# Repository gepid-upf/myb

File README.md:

# Move Your Body

Code provided in this repository gets the raw data from MPU-6050 and MAX30100, calculates a step counter and heart rate, and stores it in the ESP-32 SPIFFS to be send via bluetooth to the MYB App.

## Table of Contents

- [Components](#components)
  - [ESP 32](#esp-32)
  - [ESP-IDF](#esp-idf)
  - [MPU-6050](#mpu-6050)
  - [MAX30100](#max30100)
- [Quick Start](#quick-start)
  - [Connect](#connect)
  - [Configuration and Flash](#configuration-and-flash)
- [How It Works](#how-it-works)
- [Next Steps](#next-steps)
  - [Software](#software)
- [License](#license)
- [Acknowledgments](#acknowledgments)

## Components

To make this code work, you need the following components:

* This repository. It contains submodules, so make sure you clone it with `--recursive` option. If you have already cloned it without `--recursive`, run `git submodule update --init`.
* [ESP 32](https://espressif.com/en/products/hardware/esp32/overview) module.
* [ESP-IDF](https://github.com/espressif/esp-idf).
* [MPU-6050](https://www.invensense.com/products/motion-tracking/6-axis/mpu-6050/) module.
* [MAX30100](https://www.maximintegrated.com/en/products/sensors/MAX30100.html) module.

### ESP 32

Any ESP 32 module should work.

### ESP-IDF

Configure your PC according to [ESP 32 Documentation](https://docs.espressif.com/projects/esp-idf/en/latest/?badge=latest?badge=latest). Windows, Linux and Mac OS are supported.

### MPU-6050

This example has been tested with a MPU-6050. 

The MPU-6000 should work aswell.

### MAX30100

Any MAX30100 module should work.

## Quick Start

If you have your components ready, follow this section to [connect](#connect) the components to the ESP 32 module, [flash](#configuration-and-flash) the application to the ESP 32 and monitor the data.

### Connect

The pins used in this project to connect the ESP 32 to the MPU-6050 and MAX30100 are shown in the table below. The pinout can be adjusted in the software.

| Interface | MPU-6050 Pin | MAX30100 Pin | ESP 32 DevKitC Pin Mapping |
| :--- | :---: | :---: | :---: |
| I2C Serial Clock | SCL | SCL | IO25 |
| I2C Serial Data | SDA | SDA | IO26 |
| Power Supply 3.3V | VCC | VIN | 3V3 |
| Ground | GND | GND | GND |

Notes:

If the sensors are not communicating with the ESP 32, consider adding 10kΩ pull-up resistors to the SCL and SDA lines.

If you're using ESP 32 on Windows and is having the [ESP 32 Reset to Bootloader](https://github.com/espressif/esptool/issues/136) issue, add a 2.2uF capacitor conencted between GND and EN pins of ESP 32 module.

### Configuration and Flash

1. Clone the code provided in this repository to your PC.

2. To use the SPIFFS, you need a tool to create the SPIFFS partition image - we recommend using [igrr](https://github.com/igrr)'s [mkspiffs](https://github.com/igrr/mkspiffs).
After creating the SPIFFS image, use the `esptool` to flash the image binary to the module.
If you're gonna use the `partitions.csv` file, use the following configuration:
```
BLOCK SIZE = 4096
PAGE SIZE = 256
PARTITION SIZE = 0x2F0000
PARTITION OFFSET = 0x110000
```

3. On the `menuconfig`, use the following options:
```
Flash size: 4MB
Partition Table: Custom Partition Table CSV (choose the partitions.csv file)
```

4. Compile with the latest ESP-IDF installed from GitHub and download it to the module.

## How it Works

### Software

The software has 3 libraries, all located in the components folder:
* [esp32_i2c_rw.c](https://github.com/gabrielbvicari/esp32-i2c_rw/blob/f532d6a554dc2f2daa3954b597072ecb48354688/esp32_i2c_rw.c) and [include/esp32_i2c_rw.h](https://github.com/gabrielbvicari/esp32-i2c_rw/blob/f532d6a554dc2f2daa3954b597072ecb48354688/include/esp32_i2c_rw/esp32_i2c_rw.h) - implementation of the I2C protocol used by the [MPU-6050](https://github.com/gabrielbvicari/esp32-mpu6050) library.

* [mpu6050.c](https://github.com/gabrielbvicari/esp32-mpu6050/blob/fa99df4a75917e85b31b20e94344acca3d00d556/mpu6050.c), [include/mpu6050.h](https://github.com/gabrielbvicari/esp32-mpu6050/blob/fa99df4a75917e85b31b20e94344acca3d00d556/include/mpu6050/mpu6050.h) and [include/mpu6050_registers.h](https://github.com/gabrielbvicari/esp32-mpu6050/blob/fa99df4a75917e85b31b20e94344acca3d00d556/include/mpu6050/mpu6050_registers.h) - definition of the registers of the MPU-6050, setters/getters functions for the registers aswell as functions of calibration and self-test.

* [max30100.c](https://github.com/aedalzotto/esp32-max30100/blob/2585aa70b25955ecb60d2d8fb26c5cbb76526d65/max30100.c), [include/max30100.h](https://github.com/aedalzotto/esp32-max30100/blob/2585aa70b25955ecb60d2d8fb26c5cbb76526d65/include/max30100/max30100.h) and [include/registers.h](https://github.com/aedalzotto/esp32-max30100/blob/2585aa70b25955ecb60d2d8fb26c5cbb76526d65/include/max30100/registers.h) - definition of the registers of the MAX3010, setters/getters functions for the registers aswell as implementations of filters (Butterworth, DC Removal and Moving Average).

* component.mk - files used by C `make` command to access component during compilation.

Application is executed from [main.c](main/main.c) file located in main folder.
The main file has a step counter function, as well as log functions and routines that store the readings in the SPIFFS.

## Next Steps

Add the GATT Bluetooth functionality to send the data stored in the SPIFFS to the MYB app.

## License

This project is licensed under the MIT License - see the LICENSE.md file for details.

## Acknowledgments

This application is using code based on:

* MPU-6050 implementation for Arduino by [Jeff Rowberg](https://www.i2cdevlib.com).
* MAX30100 implementation for Arduino by [Raivis Strogonovs](https://morf.lv/).

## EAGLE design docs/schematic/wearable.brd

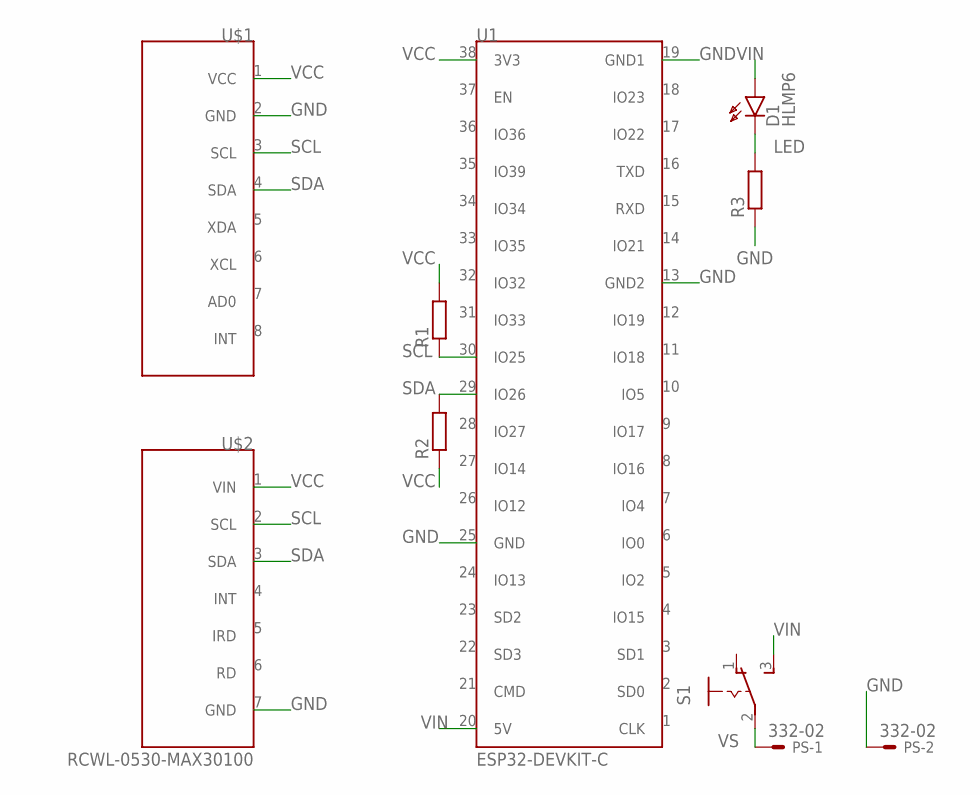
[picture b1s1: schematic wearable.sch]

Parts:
D1: HLMP6
PS: 332-02
R1, R2, R3: R-EU_0207/10; 0207/10
S1: 255SB
U1: ESP32-DEVKIT-C; ESP32
U$1: GY-521-MPU-6050; GY-521
U$2: RCWL-0530-MAX30100; RCWL-0530

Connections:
GND: PS.2, R3.1, U1.13 (GND2), U1.19 (GND1), U1.25 (GND), U$1.2 (GND), U$2.7 (GND)
LED: D1.K, R3.2
SCL: R1.1, U1.30 (IO25), U$1.3 (SCL), U$2.2 (SCL)
SDA: R2.2, U1.29 (IO26), U$1.4 (SDA), U$2.3 (SDA)
VCC: R1.2, R2.1, U1.38 (3V3), U$1.1 (VCC), U$2.1 (VIN)
VIN: D1.A, S1.3 (S), U1.20 (5V)
VS: PS.1, S1.2

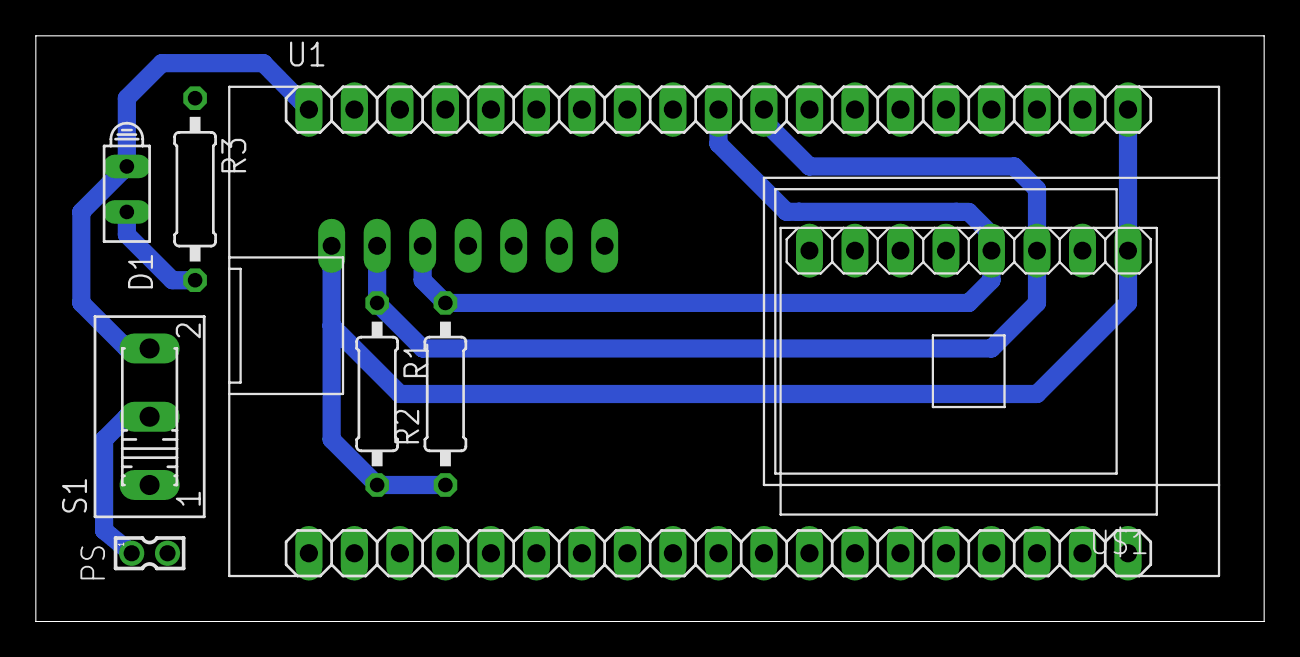
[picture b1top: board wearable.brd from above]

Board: 2 copper layers, 68.6 x 32.7 mm, 9 parts (1 on the bottom side), 7 nets.

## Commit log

2019-04-22 Initial commit.
2019-04-22 Modified LICENSE.md.
2019-04-22 Changed LICENSE.
2019-04-22 Updated LICENSE.
2019-04-22 Deleted LICENSE.md.
2019-04-22 Updated README.md.
2019-04-24 Fixed ESP_LOG messages.
2019-04-25 Fixed errors with the SPIFFS.
2019-05-02 Fixed SPIFFS and log messages.
2019-05-09 Added bluetooth functionality.
2019-05-09 Updated gitignore.
2019-05-09 Removed binary and instruction file.
2019-05-09 Added partitions.csv.
2019-05-09 removed ble for testing
2019-05-09 fixed includes
2019-05-09 fix copyright to 2019
2019-05-09 configured max30100
2019-05-09 added updated max30100 as submodule
2019-05-15 remove old lib
2019-05-15 Added submodules.
2019-05-20 Removed submodules.
2019-05-20 Updated .gitignore.
2019-05-20 Added wiring image.
2019-05-20 Update README.md.
2019-05-21 Fixed log messages.
2019-07-02 update submodules
2019-07-02 Add schematic.
